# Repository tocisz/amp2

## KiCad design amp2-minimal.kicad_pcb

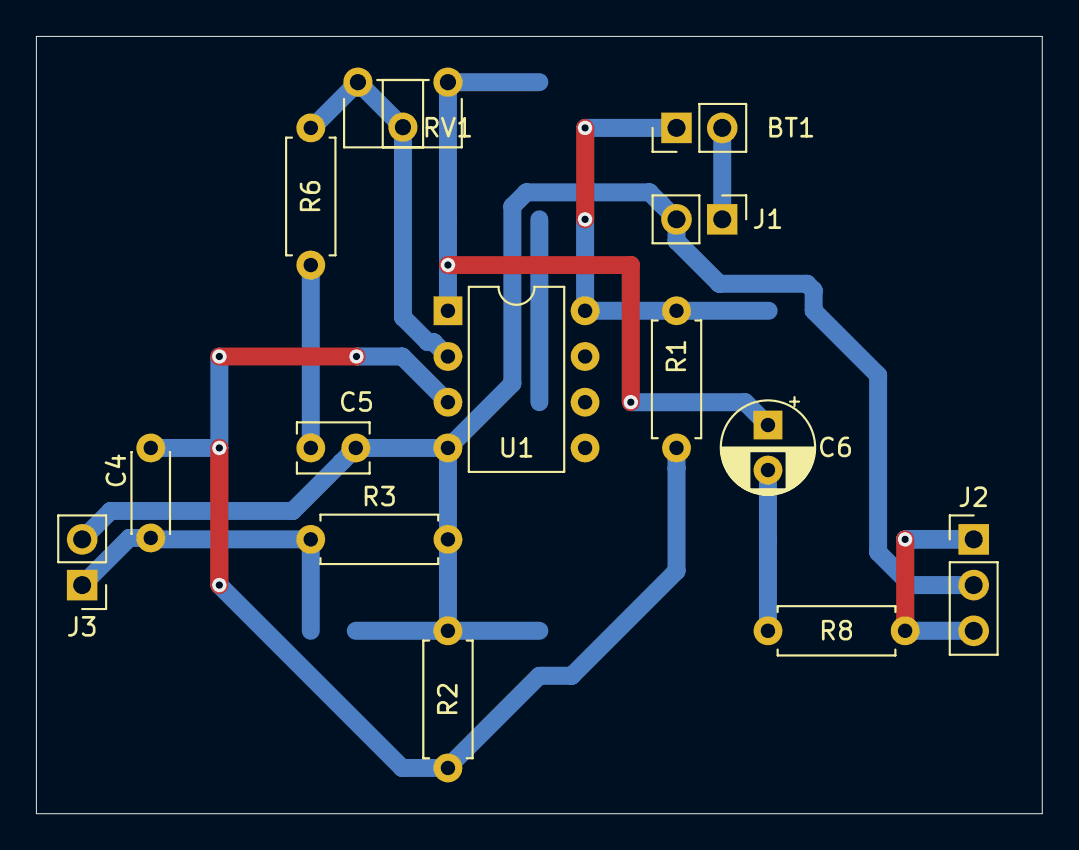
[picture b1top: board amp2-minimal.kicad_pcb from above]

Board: 2 copper layers, 55.9 x 43.2 mm, 14 parts (0 on the bottom side), 10 nets.

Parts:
BT1: Battery; PinHeader_1x02_P2.54mm_Vertical
C4: 100n; C_Disc_D4.3mm_W1.9mm_P5.00mm
C5: 10u; C_Disc_D3.8mm_W2.6mm_P2.50mm
C6: 100u; CP_Radial_D5.0mm_P2.50mm
J1, J3: Conn_01x02_Male; PinHeader_1x02_P2.54mm_Vertical
J2: Conn_01x03_Male; PinHeader_1x03_P2.54mm_Vertical
R1, R2, R3: 1M; R_Axial_DIN0207_L6.3mm_D2.5mm_P7.62mm_Horizontal
R6: 100k; R_Axial_DIN0207_L6.3mm_D2.5mm_P7.62mm_Horizontal
R8: 50; R_Axial_DIN0207_L6.3mm_D2.5mm_P7.62mm_Horizontal
RV1: 220k; Potentiometer_ACP_CA6-H2,5_Horizontal
U1: LM358; DIP-8_W7.62mm

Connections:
/+9V: BT1.1, R1.1, U1.8
GND: C5.2, J1.2, J2.2, J3.2, R2.2, R3.2, U1.4
unnamed: BT1.2, J1.1
unnamed: C4.1, R1.2, R2.1, U1.3
unnamed: C4.2, J3.1, R3.1
unnamed: C5.1, R6.2
unnamed: C6.1, RV1.1, U1.1
unnamed: C6.2, R8.2
unnamed: J2.1, J2.3, R8.1
unnamed: R6.1, RV1.2, RV1.3, U1.2

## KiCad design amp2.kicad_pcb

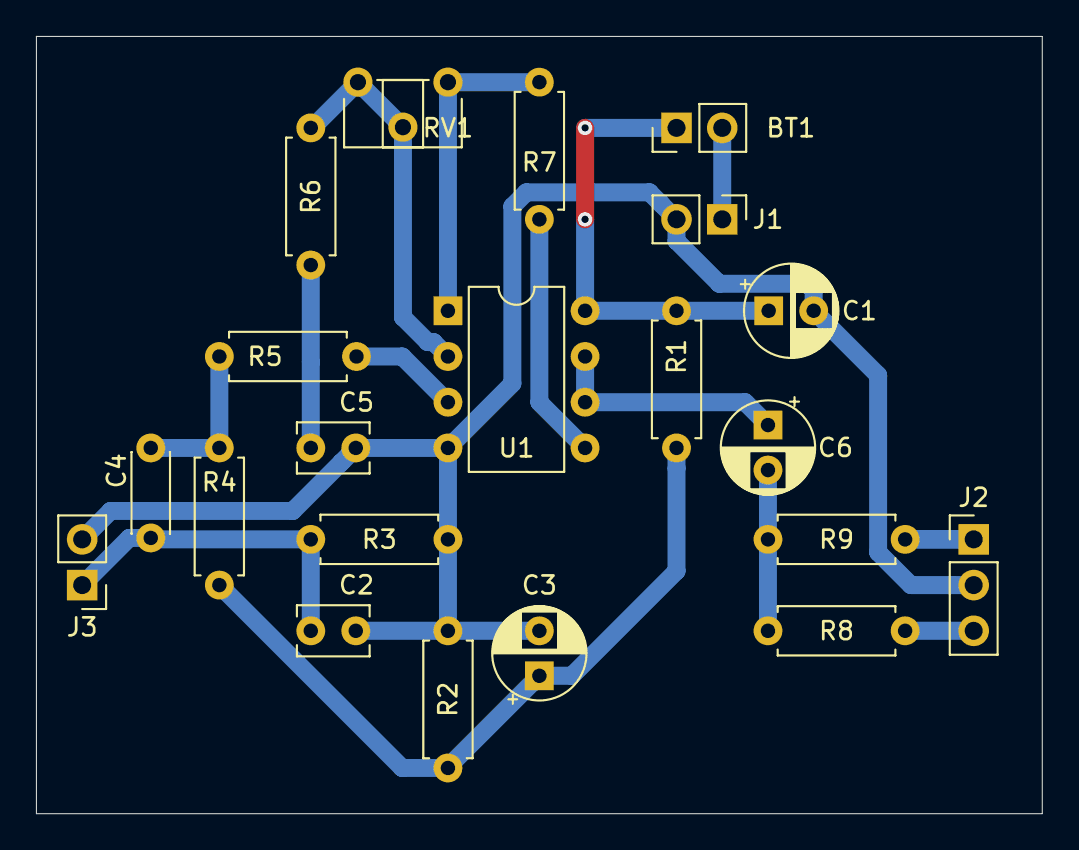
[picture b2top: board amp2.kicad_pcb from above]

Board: 2 copper layers, 55.9 x 43.2 mm, 21 parts (0 on the bottom side), 15 nets.

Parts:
BT1: Battery; PinHeader_1x02_P2.54mm_Vertical
C1, C3, C6: 100u; CP_Radial_D5.0mm_P2.50mm
C2: 220p; C_Disc_D3.8mm_W2.6mm_P2.50mm
C4: 2.2n; C_Disc_D4.3mm_W1.9mm_P5.00mm
C5: 220n; C_Disc_D3.8mm_W2.6mm_P2.50mm
J1, J3: Conn_01x02_Male; PinHeader_1x02_P2.54mm_Vertical
J2: Conn_01x03_Male; PinHeader_1x03_P2.54mm_Vertical
R1, R2: 100k; R_Axial_DIN0207_L6.3mm_D2.5mm_P7.62mm_Horizontal
R3, R4: 1M; R_Axial_DIN0207_L6.3mm_D2.5mm_P7.62mm_Horizontal
R5: 1k; R_Axial_DIN0207_L6.3mm_D2.5mm_P7.62mm_Horizontal
R6, R7: 10k; R_Axial_DIN0207_L6.3mm_D2.5mm_P7.62mm_Horizontal
R8, R9: 100; R_Axial_DIN0207_L6.3mm_D2.5mm_P7.62mm_Horizontal
RV1: 100k; Potentiometer_ACP_CA6-H2,5_Horizontal
U1: LM358; DIP-8_W7.62mm

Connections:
/+9V: BT1.1, C1.1, R1.1, U1.8
GND: C1.2, C2.2, C3.2, C5.2, J1.2, J2.2, J3.2, R2.2, R3.2, U1.4
unnamed: BT1.2, J1.1
unnamed: C2.1, C4.2, J3.1, R3.1
unnamed: C3.1, R1.2, R2.1, R4.1
unnamed: C4.1, R4.2, R5.2
unnamed: C5.1, R6.2
unnamed: C6.1, U1.6, U1.7
unnamed: C6.2, R8.2, R9.2
unnamed: J2.1, R9.1
unnamed: J2.3, R8.1
unnamed: R5.1, U1.3
unnamed: R6.1, RV1.2, RV1.3, U1.2
unnamed: R7.1, U1.5
unnamed: R7.2, RV1.1, U1.1

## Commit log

2022-03-13 init project
